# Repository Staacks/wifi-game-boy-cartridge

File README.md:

# wifi-game-boy-cartridge
A WiFi cartridge for the original Game Boy.

This open source and open hardware Game Boy cartridge uses an ESP8266 to allow WiFi access for custom Game Boy code. First demos include accessing Wikipedia articles from the Game Boy.

Details and instructions can be found on https://there.oughta.be/a/wifi-game-boy-cartridge and an overview is given in the following video:

Also, another article and video have been published on streaming video through this cartridge, which can be found at https://there.oughta.be/gta5-for-the-game-boy and in this video:

If you have pull-requests, bug reports or want to contribute new case designs, please do not hesitate to open an issue. For generic discussions, "show and tell" and if you are looking for support for something that is not a problem in the code here, I would recommend [r/thereoughtabe on reddit](https://www.reddit.com/r/thereoughtabe/).

# Important notice

Please read the resources above carefully and understand the limitations of this project. The brown-out issues have never been resolved and this is more a prove of concept than a consumer product. If you still want to try it yourself, please also note that rgbasm has changed a lot since this project was written and that its current version is no longer compatible with the asm files provided here. You may need to revert to rgbasm 0.5.2 to build them. 

# Short overview of the demos

As the number of demos keeps growing and some of them are just a quick experiment, you can find a few notes here:

## color-stream

This is the code for streaming videos to the Game Boy Color as shown in [in this little video](https://www.youtube.com/watch?v=kHexmGR_rPY). The code is supposed to detect if the cart is in a classic Game Boy (DMG) or a Game Boy color and both, the EEPROM code as well as the ESP8266 code should react accordingly. However, you have to use the right Python script, i.e. `video-stream` or `game-stream` for the original Game Boy or `color-stream` for a Game Boy color.

Note, that this has not been tested much and still has a few glitches. Also note, that I ran into an ffmpeg problem that prevented me from streaming screen captures on Linux (x11grab).

## serial

The oldest demo from the first video. When this is running, the Game Boy should show your IP address and you can connect to it with a telnet client. You can send text between Game Boy and PC and that's it. Note that there is an error in the way the data pins are initialized, causing them to run in open drain mode, which is ok, except for the highest bit which has an external pull-down and therefore stays low forever. For this demo, it does not matter because the character map does not have anything above the 7bit ASCII map anyways, but if you ever need the eighth bit, look at the streaming videos for how to initialize this correctly.

## stream

The streaming code on which the second video (playing GTA5) is based. It allows to show a video stream on the Game Boy and sends back key presses. You need to feed it with one of the Python scripts, either `video-stream.py` or `game-stream.py`. The buttons seem to generate a few ghost presses, which should be fixed by doing a few more readouts for the buttons (not tested).

## wiki

The Wikipedia demo from the first video. Once it has started, you can press start to get an on-screen keyboard, enter the title of a Wikipedia article and press start again to fetch an excerpt of that article. Pressing A shows you the remainder of the article, if any. Just like with the serial demo above, there is an error in the way the data pins are initialized, causing them to run in open drain mode, which is ok, except for the highest bit which has an external pull-down and therefore stays low forever. For this demo, it does not matter because the character map does not have anything above the 7bit ASCII map anyways, but if you ever need the eighth bit, look at the streaming videos for how to initialize this correctly.

# License
The code and the PCB design are released under the GNU General Public Licence 3. The only exception is the cartridge model for the 3d print, which is based on a [Game Boy cartridge by DomesticHacks on Thingiverse](https://www.thingiverse.com/thing:107841), which is released under a CC-BY-NC-SA license, so I have to publish my derived work under CC-BY-NC-SA, too.

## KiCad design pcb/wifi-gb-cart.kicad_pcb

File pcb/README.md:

# Notes on the PCB design

There are two known possible issues in this design, which you should be aware of when ordering or manufacturing this PCB:
* Some of the 3V3 lines in the top left corner are done es part of an auto-fill area. This works perfectly in KiCad, is properly exported to Gerber files and also passes bug tests with the net list. However, when I ordered from aisler.net where you upload the KiCad file instead of Gerber files, the smaller 3V3 connections were lost. Since this worked in KiCad itself, I think it is a bug in Aisler's renderer, but unfortunately, they did not reply to my questions about this issue.
* I heavily use vias in solder pads. I read that this is bad practice as it might be a problem for automatic manufacturing processes, but fine for hand-soldering. As I did the latter I did not notice any problems, but you should be aware if you use a different process.

# Licenses
This design is licensed under the GNU General Public License 3.0. See LICENSE file in this directory.

This project includes KiCad libraries and footprints from external sources with following license notices:

## From https://github.com/Gekkio/gb-hardware

This cartridge design uses the connector of Gekkio's GB-CART32K-A design, which is licensed under CC-BY-4.0.

## From https://github.com/adamgreig/agg-kicad

Copyright 2015, 2016 Adam Greig

Permission is hereby granted, free of charge, to any person obtaining a copy of this software and associated documentation files (the "Software"), to deal in the Software without restriction, including without limitation the rights to use, copy, modify, merge, publish, distribute, sublicense, and/or sell copies of the Software, and to permit persons to whom the Software is furnished to do so, subject to the following conditions:

The above copyright notice and this permission notice shall be included in all copies or substantial portions of the Software.

THE SOFTWARE IS PROVIDED "AS IS", WITHOUT WARRANTY OF ANY KIND, EXPRESS OR IMPLIED, INCLUDING BUT NOT LIMITED TO THE WARRANTIES OF MERCHANTABILITY, FITNESS FOR A PARTICULAR PURPOSE AND NONINFRINGEMENT. IN NO EVENT SHALL THE AUTHORS OR COPYRIGHT HOLDERS BE LIABLE FOR ANY CLAIM, DAMAGES OR OTHER LIABILITY, WHETHER IN AN ACTION OF CONTRACT, TORT OR OTHERWISE, ARISING FROM, OUT OF OR IN CONNECTION WITH THE SOFTWARE OR THE USE OR OTHER DEALINGS IN THE SOFTWARE.

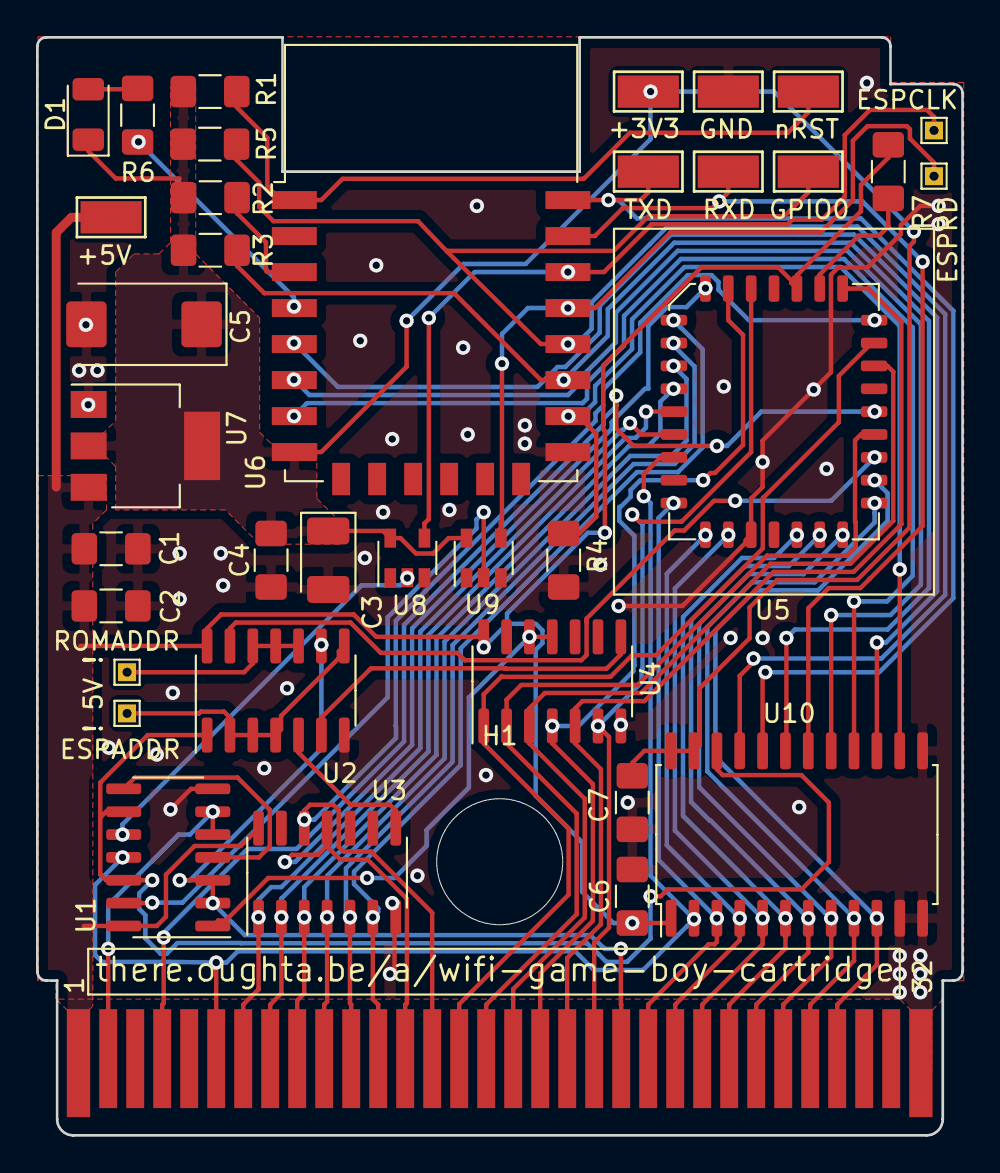
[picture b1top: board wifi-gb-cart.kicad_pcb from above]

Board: 2 copper layers, 51.4 x 61.0 mm, 38 parts (0 on the bottom side), 54 nets.

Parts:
+3V3, +5V: TestPoint; TestPoint_Keystone_5015_Micro-Minature
C1: 10uF; C_1206_3216Metric_Pad1.42x1.75mm_HandSolder
C2, C4, C6, C7: 100nF; C_1206_3216Metric_Pad1.42x1.75mm_HandSolder
C3: 100uF; CP_EIA-3528-12_Kemet-T_Pad1.50x2.35mm_HandSolder
C5: 680uF; CP_EIA-7343-43_Kemet-X_Pad2.25x2.55mm_HandSolder
D1: LED BLUE; LED_1206_3216Metric
ESPADDR: TestPoint; TestPoint_THTPad_1.0x1.0mm_Drill0.5mm
ESPCLK: TestPoint; TestPoint_THTPad_1.0x1.0mm_Drill0.5mm
ESPRD: TestPoint; TestPoint_THTPad_1.0x1.0mm_Drill0.5mm
GND: TestPoint; TestPoint_Keystone_5015_Micro-Minature
GPIO0: TestPoint; TestPoint_Keystone_5015_Micro-Minature
H1: MountingHole; MountingHole_7mm
J1: Conn_01x32; cartridge_PCBedge
R1, R2, R3, R4, R5, R7: 12k; R_1206_3216Metric_Pad1.42x1.75mm_HandSolder
R6: 330; R_1206_3216Metric_Pad1.42x1.75mm_HandSolder
ROMADDR: TestPoint; TestPoint_THTPad_1.0x1.0mm_Drill0.5mm
RXD: TestPoint; TestPoint_Keystone_5015_Micro-Minature
TXD: TestPoint; TestPoint_Keystone_5015_Micro-Minature
U1, U2: 74AHCT02D; SOIC-14_3.9x8.7mm_P1.27mm
U3, U4: 74AHCT30D; SOIC-14_3.9x8.7mm_P1.27mm
U5: 28C256; PLCC-32_11.4x14.0mm_P1.27mm_SOCKET
U6: ESP-12F; ESP-12E
U7: NCP1117-3.3_SOT223; SOT-223-3_TabPin2
U8, U9: SN74LV1T34DBV; SOT-23-5
U10: SN74LVC4245ADWRG4; SOIC-24W_7.5x15.4mm_P1.27mm
nRST: TestPoint; TestPoint_Keystone_5015_Micro-Minature

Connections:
+3V3: +3V3.1, C3.1, C4.1, C5.1, C7.1, D1.1, R1.1, R2.2, R3.1, R5.1, U6.8, U7.2, U8.5, U9.5, U10.23, U10.24
+5V: +5V.1, C1.1, C2.1, C6.1, J1.1, R7.2, U1.14, U2.14, U3.14, U4.14, U5.32, U7.3, U10.1
A0: J1.6, U1.11, U5.11, U10.2
A1: J1.7, U3.1, U5.10
A2: J1.8, U3.2, U5.9
A3: J1.9, U3.3, U5.8
A4: J1.10, U3.4, U5.7
A5: J1.11, U3.5, U5.6
A6: J1.12, U3.6, U5.5
A7: J1.13, U3.11, U5.4
A8: J1.14, U3.12, U5.29
A9: J1.15, U4.1, U5.28
A10: J1.16, U4.2, U5.24
A11: J1.17, U4.3, U5.27
A12: J1.18, U4.4, U5.3
A13: J1.19, U4.5, U5.30
A14: J1.20, U4.6, U5.2
A15: J1.21, U1.2, U1.3, U2.9
D0: J1.22, U5.13, U10.3
D0_3V3: GPIO0.1, R5.2, U6.18, U10.21
D1: J1.23, U5.14, U10.4
D1_3V3: TXD.1, U6.22, U10.20
D2: J1.24, U5.15, U10.5
D2_3V3: R3.2, U6.17, U10.19
D3: J1.25, U5.18, U10.6
D3_3V3: RXD.1, U6.21, U10.18
D4: J1.26, U5.19, U10.7
D4_3V3: U6.6, U10.17
D5: J1.27, U5.20, U10.8
D5_3V3: U6.7, U10.16
D6: J1.28, U5.21, U10.9
D6_3V3: U6.5, U10.15
D7: J1.29, U5.22, U10.10
D7_3V3: R4.2, U6.16, U10.14
ESPADDR: ESPADDR.1, U2.2, U2.3, U2.4, U2.8
ESPCLK: U1.10, U8.2
ESPCLK_3V3: ESPCLK.1, U6.20, U8.4
ESPRD: U1.13, U9.2
ESPRD_3V3: ESPRD.1, U6.19, U9.4
GBCLK: J1.2, U1.5, U1.6
GBRD: J1.4, U5.25
GND: C1.2, C2.2, C3.2, C4.2, C5.2, C6.2, C7.2, GND.1, J1.32, R4.1, U1.7, U2.7, U3.7, U4.7, U5.16, U6.15, U7.1, U8.3, U9.3, U10.11, U10.12, U10.13
unnamed: D1.2, R6.1
unnamed: R2.1, U6.3
unnamed: R6.2, U6.4
unnamed: R7.1, U5.31
unnamed: U1.1, U4.11, U4.12
unnamed: U1.4, U1.8
unnamed: U2.5, U3.8
unnamed: U2.6, U4.8
ROMADDR: ROMADDR.1, U2.10, U2.11, U2.12
nESPADDR: U1.9, U1.12, U2.1, U10.22
nROMADDR: U2.13, U5.23
nRST: R1.2, U6.1, nRST.1

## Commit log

2021-12-14 Initial commit.
2021-12-14 Create LICENSE
2021-12-14 Remove unused KiCad library.
2021-12-15 Add PNG preview of PCB schematic.
2022-01-08 Add NC drill files to PCB gerber folder. (Fixing issue #1)
2022-01-13 Add source for new streaming demos.
2022-01-26 Add code for video streaming to the Game Boy Color. This has not been tested much and still has a few glitches.
2022-01-26 Add BOM in CSV format. (issue #3)
2022-02-09 Several small improvements to GBC streaming: - Slightly more wiggle room in interrupts for more robust timing. - Reduce WiFi TX power (this fixes most of the visual glitches and somewhat improves the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
2025-01-03 Upgrade PCB to KiCad 8 and add interactive HTML bom.
